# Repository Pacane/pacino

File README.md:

# Pacino

A hand-wired wireless split keyboard you print, screw together and solder — no main PCB.
Parametric OpenSCAD case + switch plate, with a build pipeline that produces **real STEP solids**
(via FreeCAD) so everything is editable in Fusion 360 as B-rep geometry, not as a mesh.
If you would rather not hand-wire it, the same design has a **slim build**: an 11.5 mm case around a
reversible PCB that is generated from this model and ready to order — [see below](#the-slim-build-a-real-pcb-115-mm).

Named after (and descended from) the [cheapino](https://github.com/tompi/cheapino), whose column
stagger and thumb-cluster geometry it borrows; hardware-wise it runs a nice!nano-compatible
nRF52840, Kailh hot-swap sockets on Amoeba-King single-key PCBs, and ZMK.

*20 keys per half (40 total): 5 columns + 2 extra keys, with the nice!view display. 145 × 120 mm.*

*23 keys per half (46 total): the optional 6th outer column, same display. 164 × 120 mm.*

*The minimal build — 18 keys per half (36 total), no extra keys, no display. 145 × 120 mm.*

All three are the same scale. The display costs no width: stacked over the nano, a build with it is
exactly as wide as one without. Renders of every other combination are
[at the bottom](#variant-gallery).

*The slim build: the same 40 keys over a reversible PCB, **11.5 mm** to the plate top instead of 17.5,
and flat — the cell lies in a well under the board. The controller sits flush in the plate window.*

**The default design:** a cheapino-style 3×5 (+2) + 3-thumb column-stagger layout on a clean
19.05 mm **MX** grid with **1.25u thumbs**, an **electronics bay** beside the inner column that
holds a **LiPo** (sunk into a well in the case floor — a 902030 by default), a **nice!nano**
(**flipped component-side down** in a cradle that is part of the plate, fully enclosed, USB out
through a notch in the wall) and a **reset button and power slide switch** in pockets in the
plate, laid out for **hand-wiring**. A **nice!view** mount (flush in the plate *directly over* the
nano, clamped by a screw-down bezel, so it costs no extra width) is in the model but off by default:
mounting bosses live in the walls, not in the matrix, and there is ~3 mm under the switch pins.
A PCB-sandwich build is a switch away.

```
keyboard.scad            the model — all parameters at the top, Customizer-friendly (parts: case, plate, section; bezel with nice_view)
layouts/cheapino.scad    generated from ../cheapino/pcb/cheapino.kicad_pcb  (exact positions, if you want them)
layouts/badtemper.scad   generated from ../badtemper2/BadTemper.kicad_pcb
tools/kicad_layout.py    KiCad .kicad_pcb -> layouts/*.scad  (switches, holes, MCU, Edge.Cuts polygon)
tools/pcb_gen.py         the slim build's PCBs: model -> pcb/*/ boards + footprint libs + gerbers
pcb/flat/  pcb/pod/     those two KiCad projects (generated, DRC-clean; each has its own README,
                         gerber zip and renders).  part = "pcb_test" prints a stand-in to fit first
tools/csg2step.py        OpenSCAD .csg -> STEP, runs inside FreeCAD
tools/svg_polygon.py     helper: bakes the cavity outline to a polygon for the FreeCAD pass
build.sh                 builds everything into out/
out/                     STEP / 3MF / STL / DXF / PNG — regenerate any time, never hand-edit
CHANGELOG.md             what changed since you printed — and whether you need to reprint, re-order or reflash
```

## Pick a ready-made variant

[`variants/`](variants/) holds every combination of the four options — 5 or 6 columns, with or
without the two extra keys, 902030 or 103450 battery, with or without nice!view — each as
`case_*` / `plate_*` STEP + 3MF for both halves (plus a bezel for display versions) and previews.
The index in [`variants/README.md`](variants/README.md) lists sizes; `./build_variants.sh`
regenerates them all.

## Quick start

```sh
./build.sh            # everything: step, mesh, dxf, png  (~40 s)
./build.sh step       # just the STEP files
SCAD_ARGS='-D battery=[34,50,10.5]' ./build.sh    # any parameter override, e.g. the 2000 mAh cell
```

Or open `keyboard.scad` in OpenSCAD and use the Customizer (`Window ▸ Customizer`).
`part` selects what is shown/exported (`assembly`, `section`, `case`, `plate`, the 2D profiles),
`side` picks `left` / `right` / `both`, `explode` lifts the plate.

Outputs per side: `case_*` and `plate_*` as `.step` (Fusion) and `.3mf` / `.stl` (slicer),
`*_2d_*.dxf` profiles for sketches, and `preview_*.png` (assembly, exploded, top, case, plate,
both halves, section through the bay). `WITH_DISPLAY=1 ./build.sh` additionally builds the
nice!view version (`case_display_*`, `plate_display_*`, `bezel_*`); in the Customizer that is the
`nice_view` switch.

## The layout

`grid_stagger = [0, 10, 16.4, 10, 7.5]` is the cheapino's column stagger (its PCB is already
19.0 mm MX pitch) snapped to 19.05. The thumb cluster starts where the cheapino's does
(`71.5, -15.5`) but uses **1.25u caps standing portrait** — long side pointing up at the columns —
fanned −10° / −22° / −34° around the thumb (key rotation = 90° + fan) at a 21.8 mm pitch along
the arc: `[[71.5,-15.5,80,1.25], [92.5,-21.5,68,1.25], [111.7,-31.7,56,1.25]]`. That gives
~1.5 mm between caps at their lower ends (they diverge towards the top, as a radial fan does) and
1.7 mm to the bottom row. Edit `grid_thumbs` to shift or re-fan the cluster; keep the rotation
as 90 + fan so the caps stay portrait.

**Extra keys.** `grid_extra_keys = [[1, -1], [2, -1]]` adds a short fourth row under the ring and
middle columns (under X/C on the left half, ,/. on the right) — 38 keys per pair. `[]` removes them;
any `[column, row]` pair on the grid works.

**Sixth column.** `grid_outer_col = true` adds a column outside the pinky (Corne-style 3×6), with
its own `grid_outer_stagger` (0 = same as the pinky). The left-edge bosses and bumpons follow it; the
half grows to 164 mm wide. Build it alongside the default with
`SUFFIX=_6col SCAD_ARGS='-D grid_outer_col=true' ./build.sh`.

**Hand-wiring.** Eight 6 mm bosses sit 0.5 mm inside the inner wall line so they merge into the
wall and the whole matrix area is free for diodes and wires (each boss was checked for ≥ 2 mm to
every switch body, ≥ 1 mm to the battery, and clear of the MCU cradle and the keycap footprints
so the screw heads are reachable). Under the plate there are 10 mm: MX body + pins take 8.3 from
the plate top, leaving ~3 mm under the pins. The bay has ~8 mm of floor to the right of the battery and 4 mm below it for routing,
and its open fence end faces the nice!nano.

Set `layout = "cheapino"` or `"badtemper"` to use the exact positions extracted from those
boards instead (`cavity_from = "pcb"` then follows that board's Edge.Cuts).

## The electronics bay

```
bay_left / bay_top_y = 86.5 / 61   the bay hangs from its top edge (USB at the top); size is automatic
battery_type = "902030"            the cell (902030 / 103450 / 604060 / custom), bottom-left of the bay, in a 3 mm fence
mcu_size   = [18, 33]              nice!nano at the top of the bay over the battery (measured on a SuperMini clone)
nv_pcb     = [14, 36, 1.6]         nice!view, right of the nano, header end down
ctrl_bay_h = 13                    reset + power strip hung below the bay, switches at its right end
```

Stack at the bay with the 902030 (z from the case underside): floor 0–2.5, with the battery well
sunk to 1.2 · battery 1.2–10.7 · 2.8 clearance for the nano's components, which now face down ·
nice!nano PCB 13.5–15.05 · 0.95 air · plate 16–17.5. The 1.3 mm the well recovers pays for the
component clearance the flip costs, so overall height is unchanged. The model warns if the board's
components would hit the battery or the board would hit the plate. `part = "section"` renders the stack as a 2D cut.

`battery_type` picks the cell and sizes the bay and the cavity depth (`cavity_depth = 0` = automatic,
battery thickness + 4): `902030` (20 × 30 × 9, 500 mAh — weeks per charge; 13.5 mm cavity),
`103450` (34 × 50 × 10, 2000 mAh; 45 × 60 bay, 14.5 mm cavity, +1 mm case height and +3 mm width — the bay reaches past the thumb cluster), `604060` (40 × 60 × 6; 10.5 mm cavity),
or `custom` with `battery_custom`. Build the 2000 mAh version alongside the default with
`SUFFIX=_2000mah SCAD_ARGS='-D battery_type="103450"' ./build.sh` → `case_2000mah_*`, `plate_2000mah_*`.
The controller charges at 100 mA by default, which is ~20 h for the 2000 mAh cell: before you fit it, bridge the
**boost** solder jumper on the back of the board (two pads by the battery pads; 500 mA on a nice!nano v2, 300 mA
on the SuperMini clones — only with a cell over 500 mAh, so not for the 902030 or 303040).

### How the nano and the battery are held

**Battery:** it drops into a **well sunk 1.3 mm into the case floor** (`battery_well_floor`), whose
walls locate it on all four sides; with the plate on, the nano 2.8 mm above it keeps it in the well. Set `battery_well_floor = 0`
instead and it sits on the floor inside a 3 mm printed fence (`battery_fence`, open at the lead end),
which costs 1.3 mm of case height — the well is the default because the flipped nano needs the room.

**nice!nano / nRF52840 clone:** it goes in **upside down** (`mcu_flipped`, the default) — components
and USB connector facing *into* the case, bare PCB back facing the plate. That protects everything on
the board, and because the wires now poke straight down through the pads into the bay, the cradle no
longer needs wire channels along the sides: the plate above it is **solid**, with no opening over the
MCU at all.

It sits in a cradle that is part of the plate: rails on both long sides, open at the USB end,
holding the board four ways —

- **sideways:** five half-round **crush ribs** per rail (`crush_rib`, 0.6 mm proud, centred on the
  pocket wall so nothing bulges outward), narrowing the 18.6 mm slot to **17.4 mm** at the ribs. An
  18.0 mm board goes in with real resistance and shaves them to a custom fit; boards up to ~18.6 mm
  crush them further. Turn `crush_rib` down for a lighter fit, up for a tighter one.
- **from below, far end:** two corner tabs under the outer 0.5 mm of the far edge, with a 10 mm gap
  between them so a SuperMini-style clone's centred reset button stays clear.
- **from below, USB end:** two posts rising from the **case floor** (`mcu_end_post`), which engage
  once the plate is screwed down.
- **from above:** a 6 mm-wide roof pad on the plate over the bare back of the board, leaving it
  0.2 mm of lift.

**To fit it: with the plate off the case, slide the board into the cradle from the open USB end
until it meets the far rail.** To remove it, push it back out through the **4 mm eject hole** in the
far rail. **Set `mcu_size` to your board's real width × length.** Before printing, check your board's
component side is clear where the cradle touches it: the far corners (outer 0.5 mm, either side of
the reset button) and the two USB-end corners.

**Wiring the nano:** solder the wires on what is now the underside — they drop straight into the bay,
no channels or routing needed. The battery leads come up out of the well right below the board.

Setting `mcu_flipped = false` restores the old component-side-up cradle: an opening through the
plate, wire channels along both long edges, and a USB slot that crosses the plate line.

### Reset button and power switch

Plain through-hole parts, both dropped into the plate from above: a **12 × 12 mm tactile switch**
with a tall plunger (reset → nano `RST` + `GND`) and an **SS12D00 slide switch** (power, in series
with the battery `+` to the nano's `B+`). Each pocket is a hole through the plate the size of the
body (+0.2 mm) with a 1.2 mm floor hanging below, with a 3.5 mm square opening around each leg
(`ctrl_leg_hole`) so the legs hang in free air below the floor and a wire can be wrapped and
soldered to them from underneath. The
tactile's body sits 2.3 mm below the plate top so ~1 mm of its 3.3 mm plunger is proud — enough to
press, hard to hit by accident; the slide's 3 mm actuator stands up for your thumbnail. Solder
wires to the legs from below. Nothing can push the parts in (they sit on the floor) and the legs
plus wires keep them from lifting; if you want belt-and-braces, a dab of glue or a 0.1 mm tighter
`ctrl_clearance` does it. `reset_body` / `power_body` / `*_legs` take the dimensions of whatever
switches you actually buy.

They sit in a **control bay** strip hung below the electronics bay (`ctrl_bay_h = 0` sizes it for
the larger switch), placed as high as the battery allows — the pockets reach up into the bay's
battery-free margin — so they stay clear of the thumb keys in both battery layouts, off the battery
(legs and wires hang free below), and add nothing to the bay's width. (The strip spans the full bay width on purpose: a narrower one leaves a pocket
between bay, column 4 and thumb key 2 that the outline smoothing turns into a hole.)

### nice!view

The nice!view has no mounting holes — on a PCB it hangs off its 5-pin header — so here it is
**clamped**. It sits vertically (header end down, the way a Corne shows it) in a pocket through the
plate, resting on two 1 mm ledges under its long edges that hang from a ring below the plate. The PCB
top ends up `nv_preload` (0.15 mm) above the plate top; the printed **bezel** (`part = "bezel"`,
2.5 mm, window sized to the glass) is screwed down onto two 5 mm bosses hanging under the plate with
M2 screws — `nv_boss_hole_d = 1.7` for self-tapping into PETG (works well; 3 mm of engagement), or
3.2 for heat-set inserts — so it clamps the PCB, not the plate. The 12.6 mm opening under the
display leaves the solder pads free. Nothing can come loose without removing two screws, and
nothing relies on a friction or snap fit.

**It sits directly on top of the nano** (`nv_stacked`, the default). That only works because the
board is flipped: the plate above it is solid, so the display can take that surface. The bay then
stays as narrow as the no-display version — the display costs **0 mm of width** instead of 11.6.

Three things follow from stacking, and the model enforces all of them:

- The bezel's screw bosses move from the display's **ends to its sides** — an end boss hangs 3 mm
  below the plate and would pass straight through the board. On the sides they clear the board by
  0.8 mm and the cradle pocket by 0.5 mm, landing in free bay space 2.3 mm above the battery.
- The support ledges are thinned (`nv_ledge_te`, 1.2 → 0.6 mm) so they clear the board's back by
  0.4 mm — and they then double as the board's hold-down, replacing the cradle roof pad that the
  display's opening cuts through.
- The display's wiring end overhangs past the board, so its five wires drop straight into the bay
  and run to the nano's pads, which now face into the bay.

The cost is servicing: getting the nano out means removing the bezel and lifting the display first.
Set `nv_stacked = false` for the old side-by-side bay (11.6 mm wider); it is also the automatic
behaviour if `mcu_flipped` is off, since an unflipped nano needs that plate area for its own opening.

### Bumpons

Eight 10.6 mm × 1 mm recesses in the underside for 10 mm self-adhesive rubber feet (`bumpon_d`,
`bumpon_clearance`, `bumpon_depth`; `bumpon_positions` for the four under the key block and thumb
cluster, two on the left edge follow the outer column, and two are placed on the bay: 8 mm in from
its top-right corner, and 12 mm up from the bottom of the control strip on the right). The floor is
2.5 mm so 1.5 mm remains under each recess.

The two bay feet and the **battery well** compete for the same floor: the well is already 1.3 mm
into it, so a recess over the well would leave 0.2 mm. With a well the cell therefore sits against
the bay's *left* wall (which doubles as the well's side) instead of 5 mm from it, keeping the bay's
right-hand corners clear, and the bay is sized so the top-right foot always fits beside the cell with
a millimetre of wall outside its recess. Each bay foot then moves outward only by what its well
forces — a couple of millimetres — and the model warns if one has nowhere to go. The wider cells pay
for it in width: the 103450's bay is 45 mm instead of 44, and its case 148 mm. A 56 mm MagSafe magnet ring (the
self-adhesive kind) goes under the index column (`magsafe_d`, `magsafe_pos`; 0 = none). It is **printed in**
(`magsafe_style = "embedded"`, the default): an annular pocket exactly as tall as the ring (`magsafe_ring_id`,
`magsafe_ring_t`; measure your ring — a 56 mm sticker ring is about 45 mm inside and 0.5–0.7 mm thick), open to the
underside through a window one layer up, so the first layer is a ledge overlapping the ring's edges by 0.8 mm
(`magsafe_lip_w`) and the steel shows through between them, 0.2 mm below the surface. Add a pause in the slicer
**before layer 5** (the model prints the height: after the layer ending at z = 0.8 mm), drop the ring in with its
exposed face **down** and the adhesive up, press it flat, and resume. Layer 5 is then laid straight onto the ring,
like a first layer on a sticky bed, with the nozzle a full layer above the steel. If supports are on, put a
support blocker over the ring: the pocket reaches the plate through the window and would otherwise be filled.
It uses 0.8 mm of the 2.5 mm floor, so it works in the slim build too, and the ring cannot come off. Being
steel, the ring has no polarity to get wrong.

Why the window: the hold improves with every tenth of a millimetre less between the ring and the mount. A
0.4 mm skin over the ring (`magsafe_skin = 0.4`) is the clean look and holds decently; a one-layer skin held
better but tears along its lines with the ring's edge behind it; the ledge is backed by the pocket wall and holds.
Don't leave air over the ring either (`magsafe_pocket_air` only pads a ring thinner than a layer multiple; keep
ledge or skin + ring + air on a layer boundary, the model notes if it isn't): the ceiling would have to bridge it,
and since a layer's lines all run one way, the ones running along the ring span 30 mm chords and sag. The bigger
lever is the ring itself: the usual sticker ring is 0.65 mm of steel, and a *magnet* ring (1.2–2 mm, 16 segments)
holds a mount in a different league — the pocket takes it the same way, but it has a right way up: hold it
against the mount first and put the face it pulls in with down.

The two stick-on alternatives: `"groove"` leaves the underside flat with a one-layer locating groove 0.3 mm
outside the ring's edge, and the ring's adhesive sticks straight to the bed-side first layer (it holds there, as on
any PETG print). `"recess"` sinks the ring 1 mm into the floor (`magsafe_depth`), but that pocket prints on
support and the adhesive does *not* hold on a support-interface surface — sand the pocket and glue the ring in.
The recess has to stay clear of the battery well, since the two cut the floor from opposite sides and would leave
0.2 mm where they overlap (the model warns). `out/preview_bottom.png` shows them all.

### How the plate attaches

The plate is the lid. The case walls end flush with the plate's underside, so the plate rests on
them all round; a 1 mm lip under the plate drops inside the walls (0.2 mm clearance) and locates it.
Eight 6 mm bosses rise from the floor to the plate underside (six around the key block, two on
the bay's right-hand corners, all half-buried in the wall so they don't intrude on the wiring), each with a
3.3 mm × 5 mm hole, with a 4.2 mm × 0.6 mm counterbore at its mouth (`boss_relief_d` / `boss_relief_h`), for an **M2 × 4 × 3.5 brass heat-set insert** — press it down until it bottoms in the counterbore, so it and the plastic it displaces sit below the boss face and the plate seats without trimming (`boss_hole_d = 1.7` if you'd
rather self-tap). **M2 × 6 screws** go down through the plate into them — the heads sit on top of
the plate, like a tray-mount case (ultra-thin hex-socket heads are ideal).

Hardware per half: 8 × M2×4×3.5 inserts, 8 × M2×6 screws, 8 × 10 mm bumpons
(+ 2 × M2×4 self-tapping screws for the bezel if you build the display version).
`variants/insert_test.3mf` (`part = "insert_test"`) is a two-minute test print — one boss as on the
case and a scrap of plate with its screw hole — to try the insert and screw before printing a case.

**M3 instead:** `screw_size = "M3"` resizes everything at once — 4.0 mm insert holes for the common
4.2 mm OD M3 inserts with a 5 mm counterbore, 3.4 mm clearance holes in the plate, and in the slim build a
6 mm spacer boss, a 4.6 mm wall channel, a 3.6 mm wall and 3.4 mm board holes. Hardware is then
8 × M3 inserts (4 mm long here, 3 mm in the slim build) and 8 × M3×6 (M3×10 slim) screws; an M3 socket
head is 5.5 mm across, so use low-profile ones. The 6 mm bosses keep 1 mm of wall around the insert —
fine for the five buried in the wall, set the three free-standing ones carefully. The bezel stays M2.

### Hot-swap with single-key PCBs

Per-key hot-swap PCBs (amoeba style) work as-is: the Kailh socket and the diode go on the underside
of each little board, the bare top face sits against the switch body, and the board hangs on the
switch — the socket grips the pins (as in any hot-swap board) and 5-pin switches' pegs locate it.
Row/column wires join the boards' `ROW`/`COL` pads underneath, below the ribs.

The classic failure with hanging boards — a switch being inserted pushes the board down instead of
into the socket — is handled by **pillars rising from the case floor** under each board's four
corners (`key_pcb_post = [2.5, 3.2]`, `key_pcb_post_gap = 0.2`). They sit inside the corner notches,
on the bare 1.3 × 2 mm patches the amoeba-king keeps clear of pads and components (its side pad rows
end 5.6 mm off-centre; the pillars start at 6.3), and stop 0.2 mm below the boards, so with the case
closed a board cannot move and a new switch's pins are forced into the socket. To swap a switch,
just pull and push with the case closed; the board stays put.

**Wiring around the pillars.** The pillars hug the *top and bottom* edges of each board (the row
boundaries), 3.5 mm long at ±7 mm from centre, so the column boundaries are completely free and the
centre 10 mm of every row boundary is free too. The amoeba-king's ROW pads are on its left/right
edges and its COL pads at the centre of its top/bottom edges: row wires go straight across the
column boundary pad-to-pad, column wires run down the board centre line between the pillar pairs —
neither comes near a pillar. The only rule: never lay a wire along a board's top/bottom edge into a
corner, because a wire on a pillar patch gets clamped in the 0.2 mm gap when the case closes.
[`docs/wiring_guide.png`](docs/wiring_guide.png) shows the underside: the inner wall and its bosses,
the boards with their pads, the pillars, the matrix, and the nice!nano with every pin named. The
matrix pins are read straight from the shield (`row-gpios` in `pacino.dtsi`, `col-gpios` in
`pacino_left.overlay`), and each row and column chain gets its own thin wire to its pin, routed
clear of pillars, bosses and wall (`tools/wiring_guide.py` regenerates it and checks every wire;
each variant directory gets its own). Orient the boards with the ROW pads towards the neighbouring
columns (the pillars are sized around that). The row wires leave the inner column straight into the
bay; the column wires collect at the thumbs' COL pads (the bottom key's, for a column without a
thumb), enter the bay beside the inner column's bottom corner and climb the far side of the nano.

`key_pcbs = true` (default) also stops the ribs 0.3 mm above the boards' top face, since the boards
are wider than the rib cells; set it to false for plain hand-wiring (no boards, no pillars). All of
this is a hand-wired idea — `build = "pcb"` ignores it, and takes its rib depth from the main board.

### Plate stiffness

A flat 1.5 mm PETG plate flexes under typing, and infill/walls can't fix that (it is already
practically solid). The plate therefore carries an **egg-crate of ribs** on its underside:
a 1.5 mm wall around every switch, 3.2–3.5 mm tall (down to the switch-body bottom, or 0.3 mm above
per-key PCBs, or the main board on the slim build), 0.3 mm outside the switch's clip zone, merging
into a grid (`plate_ribs`, `rib_w`, `rib_h`). That is roughly 5× the bending stiffness of the flat plate
at no change in case height — the ribs sit beside the switch bodies, above the pins, so wiring and
diodes (which live below the pins) are unaffected. The ribs are kept clear of the bosses and the
lip. Print the plate in 100 % infill anyway; a PLA plate with a PETG case is also a fine
combination (PLA is ~70 % stiffer than PETG).

### Printing (PETG)

- **Case:** prints as-is, bosses up, with a **pause before layer 5** to drop the MagSafe ring into its pocket
  (see [Bumpons](#bumpons)). If you print with supports on (say, for the bumpon recesses), use `case_*.bambu.3mf`
  instead: the same case as a Bambu Studio / Orca project with a support blocker already over the ring pocket
  (`tools/bambu_3mf.py` makes it from the plain 3MF) — otherwise the slicer fills the pocket through its window.
  Nothing overhangs except the open-top USB slot (bridged by the
  plate, so it can stay open) and the 1 mm bumpon recesses on the first layer.
- **Plate:** print top-side down. The cradle, the switch pockets (and the display ring and bezel
  bosses, if enabled) then point up and need no support; the keycap side gets the smooth first
  layer. The cradle's crush ribs run the full rail height, so they print as part of the rail
  perimeter. The only overhangs are the cradle's far corner tabs, the roof pad over the board and
  the pocket floors (tiny, fine in PETG).
- **Bezel** (if used): window side down.
- PETG tolerances: pockets have 0.2–0.3 mm clearance, the plate lip 0.2 mm; if your printer runs
  tight, bump `mcu_clearance` / `ctrl_clearance` to 0.4 and `lip_clearance` to 0.3. The MCU cradle
  is deliberately an interference fit — tune `crush_rib` (0.6) rather than the clearances. Self-tapping M2
  into 1.7 mm holes is a good fit for PETG; heat-set inserts also work in the 5 mm bosses.

### What sets the size

Per half (case outline), against the Bad Temper:

| | width × height |
|---|---|
| Bad Temper (choc, printed case) | 122 × 94 |
| badtemper2 MX PCB + 2 mm case | 131 × 107 |
| this (default, no display) | **145.0 × 120.2** (17.5 mm to the plate top) |
| this, with nice!view | 145.0 × 120.2 (the display stacks over the nano) |
| this, slim PCB build | 145.0 × 120.2 (**11.5 mm** to the plate top, flat; or the same with a pod for a 902030) |

Without the display the bay (nano + 902030) is narrower than the thumb cluster, so the **thumb
cluster** sets the right edge (130.5) and the bottom (−51): the cheapino position plus the portrait
1.25u fan is +12 mm lower and ~+12 mm further out than the Bad Temper's 1u thumbs. The display no
longer changes that: stacked over the nano it needs no extra bay width, so both versions are the
same size. (Side by side — `nv_stacked = false` — the nano + nice!view row is 41.2 mm and pushes
the right edge to 142.1: **+11.6 mm**.) Margins (`key_margin` 3,
`wall` 2.4) account for ~2.5 mm per side. A Bad Temper-sized half therefore needs a tighter thumb
cluster, not a different battery.

## Getting it into Fusion 360

1. **STEP (recommended).** `File ▸ Open` / `Insert ▸ Insert Derive` on `out/case_left.step`.
   One solid, true planar faces, real cylindrical holes. Edit with `Press Pull`, fillets,
   `Move Face`, or sketch on a face and cut/extrude; everything after import is in the timeline.
   Volumes are cross-checked against OpenSCAD's mesh on every build (printed by `build.sh`;
   they agree to <0.01 %).
   Note the case outline is a polygon (8 segments per 90° of rounding) because OCC's 2D
   offsetting cannot reproduce OpenSCAD's outline smoothing — see `build.sh`. Holes and bosses
   are exact cylinders.
2. **DXF profiles → fully parametric rebuild.** `Insert ▸ Insert DXF` on the XY plane:
   `cavity_2d`, `case_outline_2d`, `plate_2d`. Extrude the outline to the wall height, cut the
   cavity from `floor_t` up, add bosses at the hole centres. Slower, but you own every dimension.
3. **Mesh fallback.** `Insert ▸ Insert Mesh` with the `.3mf`, then `Mesh ▸ Convert Mesh`
   (Prismatic).

## Build modes and hardware

- `build = "plate"` (default, hand-wired): switches clip into the 1.5 mm plate, 6 mm bosses run
  from the floor to the plate underside with 3.3 mm holes for M2×4×3.5 heat-set inserts
  (`boss_hole_d = 1.7` for self-tappers); M2×6 screws through the plate (`screw_size = "M3"` for
  M3 inserts and screws throughout). `cavity_depth = 10`
  leaves room for MX bodies + pins + wiring and the battery/cradle stack.
- `build = "pcb"`: PCB sandwich, and the slimmest build at **11.5 mm**. Bosses stop at the PCB
  underside, the plate gets spacer bosses down to the PCB, MX plate-to-PCB spacing is automatic
  (5.0 mm MX / 2.2 mm Choc), the MCU sits on sockets on the PCB, the plate gets a window instead of
  the cradle, and the cell either lies flat under the board or rides in a pod on the plate over the
  controller. The boards are in [`pcb/`](pcb/) — see
  [The slim build](#the-slim-build-a-real-pcb-115-mm).
- `switch_type = "choc"` swaps pitch (18 × 17), cutout (13.8), plate thickness (1.3) and heights.
- Wall cutouts: `usb_cutout = [w, h, z-offset-from-board-top]`; `extra_cutouts` for a power
  switch etc. `[x, y, outward_angle, w, h, z]`.

## Using a different PCB or layout

```sh
python3 tools/kicad_layout.py path/to/board.kicad_pcb --prefix mykbd > layouts/mykbd.scad
```

It picks up `SW*`/`K*`/`MX*` switch footprints (position, rotation), mounting holes with
1.9–3.6 mm drills, `U1` as the MCU, and chains `Edge.Cuts` into one polygon. Add an `include`
and a `layout` option in `keyboard.scad` the way `cheapino`/`badtemper` are wired in.

## The slim build: a real PCB, 11.5 mm

`build = "pcb"` turns the same design into a **PCB sandwich**, and the boards exist: [`pcb/`](pcb/)
holds two complete, DRC-clean KiCad 9 projects with gerbers, generated from this model by
[`tools/pcb_gen.py`](tools/pcb_gen.py).

*The same board from both sides. Flip it over and the bay swaps sides — that is the right half. Each
face's silkscreen names the half you build on it, and outlines its hot-swap sockets the way round
they go in on that half. These renders come out of `tools/pcb_gen.py` with the board, so they are
always the board in the repo rather than a picture of an older one.*

**11.5 mm to the plate top** — the floor for any MX build, and 6 mm thinner than hand-wired. The
stack is 2.5 floor + 2.4 (hot-swap sockets) + 1.6 board + 5.0 (MX plate-to-PCB, fixed by the
switch), and there is nothing left to remove.

Hardware for the slim build: the bosses stop at the board, so they are only 4.9 mm tall and their insert
holes 4 mm deep with 0.9 mm of floor under them, the same 0.6 mm counterbore at the mouth — use **M2 × 3 × 3.5 heat-set inserts** (the hand-wired case
takes 4 mm ones) and **M2 × 10 screws** (1.5 plate + 3.5 spacer + 1.6 board + 3 mm of thread). Five of the
eight bosses sit on the wall line like the hand-wired ones, and since the wall keeps rising 5 mm past their
tops, their insert holes would be tucked 1.2 mm under it — so a 4 mm channel (`pcb_screw_channel`) runs up
the inside of the wall over each hole, the insert and screw drop straight in, and the slim case's wall is
3 mm (`pcb_wall`) to keep 1.5 mm behind the channel (`screw_size = "M3"`: 4.6 mm channel, 3.6 mm wall, 3.4 mm
board holes, 6 mm spacer bosses — see [How the plate attaches](#how-the-plate-attaches)). The other three (thumb end, the bay's bottom corner, and
the one by the thumb keys) stand 2.5–3 mm clear of the wall as full round bosses; the board gets three real
mounting holes there and five edge notches at the wall-line ones. Two 3 mm floor pillars (`pcb_posts`)
stand under the board between the bosses, in the column gaps clear of the sockets, switch pins and diodes,
so a 55 mm span of board is not hanging on its corners; the model warns if one is moved onto a socket, and
the board generator keeps diodes off them.

Going to M3 with a board that was made for M2 (2.2 mm holes): the screws only have to pass *through* the board,
so drill its three real holes and file its five edge notches out to 3.4 mm rather than ordering a new one. Seven
of the eight have no copper within 3.15 mm of the hole centre (only the ground pour, which any drill over 2.7 mm
exposes on the hole wall — harmless, the screw lands in a brass insert in plastic). The top-edge hole between the
middle and ring columns, at (76.2, 57.1), is the exception: the column-0 bus runs 1.45 mm from its centre on the
back, so a 3.2 mm drill would cut it. Leave that one M2 with `m2_holes = [[76.2, 57.1]]` (its insert hole,
counterbore, plate hole and board notch stay M2-sized) or leave it unscrewed — the plate rests on the wall all
round. A board generated with `screw_size = "M3"` (`tools/pcb_gen.py -D 'screw_size="M3"'`) has 3.4 mm holes
from the start.

What sets it is where the cell goes, because **below the board every millimetre of battery is a
millimetre of case**. Above it, the 3.5 mm the MX geometry hands you is free — the socketed
controller already lives there, finishing flush with the plate top, and costs no height at all.
There are two ways to spend that, and both are built:

### Flat — a 303040 under the board (the default)

There is 3.4 mm of unused space under the board in the bay: 1.3 mm of floor well plus the 2.4 mm the
hot-swap sockets need — and the bay has no switches, so nothing is using it. A cell that fits inside
it needs no pod and no cutout in the board. A **303040** (3 × 30 × 40, ~320 mAh) lies in a well in the
floor, the plate stays flat, and the controller sits flush in its window.
Parts: [`variants/5col_extra2_bat303040_pcb_flat/`](variants/5col_extra2_bat303040_pcb_flat/),
board: [`pcb/flat/`](pcb/flat/).

3.4 mm is a cliff, not a slope. A thicker cell has to poke up through the board, and in the bay that
cutout runs straight under the controller and leaves its pin rows with no board to solder to — the
model warns if you ask for it.

### Pod — the 902030 over the controller

If you want the full 500 mAh, the 902030 rides in a **pod moulded into the plate, directly over the
controller** (`battery_pod = true`): in through the MCU window from below, resting on the controller,
leads down into the bay. Same 11.5 mm case, same outline — the pod stands 11.1 mm proud of the plate,
under the keycaps, which reach 14.5.
Parts: [`variants/5col_extra2_bat902030_pcb_pod/`](variants/5col_extra2_bat902030_pcb_pod/),
board: [`pcb/pod/`](pcb/pod/).

*Every part and where it sits, in the order you assemble it. `part = "section"` cuts the stack at
`section_x` (here 111, through a thumb key and the bay at once); `explode` separates the layers —
case, cell, board, controller, plate, switches, keycaps — each by its own step, so `explode = 0` is
exactly the assembled model.*

### Test-fitting it before you order a board

`part = "pcb_test"` prints a stand-in for the PCB: the real outline and mounting notches at 1.6 mm
thick, every hole a switch's pins, pegs and centre post pass through, the controller's two socket
rows, and the reset and slide switch legs — plus bumps on the underside at the hot-swap socket's real
1.85 mm, so the 2.4 mm under the board is a real test and not an assumption. Both slim variants ship
one as `pcb_test.3mf`; it is reversible the same way the board is, so flip it over for the other half.

```sh
SCAD_ARGS='-D build="pcb"' ./build.sh          # the case and plate
openscad -D 'part="pcb_test"' -D 'build="pcb"' -o pcb_test.3mf keyboard.scad
```

Print it flat, bumps up, then turn it over into the case. It checks the outline against the walls
and bosses, that every switch's pins land in a hole, the plate-to-board spacing, where the controller
and the two switches sit, the cell's room, and the 11.5 mm — everything except the copper. What it
cannot tell you: a printed 1.6 mm sheet is floppier than FR-4, so don't judge flex by it.

### The board

20 keys, 39 nets, ~515 tracks, ~16 vias, two layers, 0.3 mm tracks / 0.2 mm clearance / 0.3 mm
smallest drill — the cheapest process any fab offers. Hot-swap sockets, SOD-123 diodes (a
through-hole 1N4148 fits the same land), the controller on 3.5 mm machined low-profile sockets under the
plate window, reset and slide switch poking up through theirs. The controller gets **bare machined pins**
(Mill-Max 3320 or diode legs) — not a pin header with a plastic body: the board has to sit directly on the
sockets, 3.5 mm + its own thickness putting its back flush with the plate top and its USB receptacle inside
the socket gap. A 2.5–3 mm header body between board and sockets lifts the whole controller by that much and
pushes the USB receptacle up into the plate at the wall. The window around the controller runs right up to the
wall line at the USB end (the receptacle overhangs the board there) and the plate's rim is cut away across the
whole window at that end (the wall's notch below stays 12 mm), so the port is open from above rather than hidden
under a bridge and no stub of rim sits over the board's corners (`usb_plate_slot`); the window has 2 mm of clearance on the other sides;
`part = "clash"` renders whatever the plate hits — it should be empty. The silkscreen outlines every
hot-swap socket on both faces, so each one goes where its outline is — and because the outlines on
the two faces are the 180° rotation of each other, the way the right half differs is visible on the
board rather than only in the instructions.

The two builds are **two boards**, not one board with an option: moving the cell moves the bay, two
of the mounting holes and the reset/power positions. They are otherwise identical — same matrix,
same footprints, same firmware; only the bay end of the outline and the parts in it differ.

Both are **reversible**: one design, flipped over for the right half. Three things pay for that, and
each board's `README.md` has the detail —

- **Switches** carry *both* MX pin diagonals and a socket land on each face; on the right half they
  go in rotated 180°, which an MX switch does not care about. (Mirroring the pin pair instead — the
  obvious way — puts two 3 mm holes 2.84 mm apart and they merge into a slot.)
- **The matrix** lands on different GPIOs per half, because flipping swaps the controller's two pin
  rows. The ten holes were chosen so both of each hole's pins are usable GPIOs, keeping
  `pro_micro 1/14/15/16` free on both halves. Hence a separate `pacino_pcb` ZMK shield. (ZMK's
  stock nice!view adapter wants pins 1/2/3 — D1 plus the OLED header's SDA/SCL — and the PCB uses
  2 and 3 for the matrix, so a display on the PCB needs its own `nice_view_spi` on the free
  14/15/16.)
- **The controller** sits on top of the board — the face opposite the sockets — component side
  down, flush in the plate window; the pin lists and the **L**/**R** marks are worked out for that.
- **Power** gets two three-pad solder jumpers (bridge to **L** or **R**). Reset needs none: it sits
  across a pin pair that is GND/RST one way up and RST/GND the other.

```sh
tools/pcb_gen.py                 # both boards, footprint libraries and gerbers
tools/pcb_gen.py --variant=flat  # just one
```

Everything on them comes from `keyboard.scad` — outline, switch positions, mounting holes, controller
and switch placement — so changing the model and re-running moves the boards with it. There is no
schematic file: the generator declares every net and every connection, and names them the way the ZMK
shield does. Each project ships a `*_gerbers.zip` ready to upload; order ten and you have five
keyboards' worth of both halves.

If you would rather draw your own board, the bootstrap files are still there:
[`docs/pcb/pacino_edge_cuts.dxf`](docs/pcb/pacino_edge_cuts.dxf) (the outline for `Edge.Cuts`) and
[`docs/pcb/pacino_placement.csv`](docs/pcb/pacino_placement.csv) (every position in KiCad
coordinates), both from `tools/kicad_placement.py`. `tools/kicad_layout.py` reads a finished
`.kicad_pcb` back so the case can follow the real board.

## Variant gallery

Every option combination, with previews, sizes and download links:
**[variants/README.md](variants/README.md)** — each directory also carries an exploded-style
`preview_assembly.png`, a `preview_top.png` and its own `wiring_guide.png`.

## Firmware (ZMK)

This repo doubles as the ZMK config — no separate zmk-config repo needed. `config/` holds the
`pacino` shield (matrix, transform, default keymap) and `build.yaml` the build matrix; pushing a
change to either makes **GitHub Actions build the firmware** (Actions tab → latest run →
artifacts → `.uf2` files for left, right and `settings_reset`). SuperMini nRF52840 clones flash
as `nice_nano_v2`: double-tap reset, drag the `.uf2` on.

The slim PCB build has its own shield, **`pacino_pcb`** (same layout, same matrix, same keymap):
the reversible board puts the matrix on a different set of GPIOs on each half, so it cannot share
`pacino_left` / `pacino_right`. Both shields are in the build matrix; take the `pacino_pcb_*`
artifacts if you built the board. The pin lists are in
[`pcb/README.md`](pcb/README.md) and `tools/pcb_gen.py` prints them.

Electrical matrix ([`docs/wiring_guide.png`](docs/wiring_guide.png) draws it pin by pin) — 5 columns × 5 rows
per half, diodes `col2row` (Amoeba-King: switch → diode → ROW pad):

| matrix | wires to | nice!nano pin |
|---|---|---|
| row 0 / 1 / 2 | top / home / bottom key row | `pro_micro` 20 / 19 / 18 |
| row 3 | the two extra keys | `pro_micro` 16 |
| row 4 | the three thumbs | `pro_micro` 10 |
| col 0…4 | pinky → inner column (each column chain includes its extra key and thumb) | `pro_micro` 9 / 8 / 7 / 6 / 5 |

Pins 1, 2 and 3 are left free: that is where ZMK's stock `nice_view_adapter` puts the nice!view
(CS on D1, MOSI and SCK on the OLED header's SDA/SCL, plus VCC and GND), so the display variant is
this same wiring plus `nice_view_adapter nice_view` after the shield in `build.yaml` — no rewiring,
and nothing to add to `config/pacino.conf` (the nice_view shield enables the display itself). Pins
14/15/16 are the AVR pro micro's SPI pins; the nRF52840 puts SPI anywhere. Edit your keymap in
`config/pacino.keymap`. The left half is the central
side. The shield covers the default 5-column + 2-extra layout; the 6-column or no-extra variants
need a matching edit to the transform and one more column pin.

## Requirements

- OpenSCAD 2025.03+ (Manifold backend) — `/Applications/OpenSCAD.app`
- FreeCAD 1.0+ for STEP — `/Applications/FreeCAD.app` (only for `build.sh step`)
- Python 3 for the tools
- KiCad 9 for the PCB — `tools/pcb_gen.py` runs itself under KiCad's bundled Python (`pcbnew`)
  and uses `kicad-cli` for the gerbers

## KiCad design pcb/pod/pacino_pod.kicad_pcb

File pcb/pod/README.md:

# pacino_pod

The board for the slim build whose cell sits **in a pod moulded into the plate, directly over the controller**.
Cell: **902030 (9.5 x 20 x 30, 500 mAh)**.  Case half: [`variants/5col_extra2_bat902030_pcb_pod`](../../variants/5col_extra2_bat902030_pcb_pod/).

The two slim builds are two boards, not one board with an option: moving the cell moves the bay, two
of the mounting holes and the reset/power positions. The matrix, the footprints and the firmware are
identical between them.

Generated by [`tools/pcb_gen.py`](../../tools/pcb_gen.py) -- **do not hand-edit
`pacino_pod.kicad_pcb`**; change the generator (or `keyboard.scad`, which the outline and every
position come from) and re-run it. There is no schematic file: the generator declares every net and
every connection, and names the nets the way the ZMK shield names them.

    tools/pcb_gen.py                 # both boards, with gerbers and renders
    tools/pcb_gen.py --variant=pod  # just this one
    tools/pcb_gen.py --no-render     # skip the raytracing while iterating

20 keys, 39 nets, 580 tracks, 21 vias. Two layers, 1.6 mm, 0.3 mm tracks,
0.2 mm clearance, 0.3 mm smallest drill -- inside every fab's cheapest process.

## One board, both halves

The board is **reversible**: build the left half with the parts on the back, flip the board over and
build the right half with the parts on the front. The silkscreen on each face says which half it is.
Three things make that work.

**Switches.** Every switch footprint carries *both* MX pin diagonals -- the normal pair and its 180
degree rotation -- and a hot-swap socket land on each face. On the right half the switches and the
sockets go in **rotated 180 degrees**; MX switches are square and their stems are symmetric, so
nothing about the feel, the keycaps or the plate changes. (Mirroring the pin pair instead, which is
the obvious way to do it, puts two 3 mm holes 2.84 mm apart -- they would merge into a slot.)

**Matrix.** The controller sits on the face *opposite* the sockets and diodes -- on top of the board,
component side towards it, flush in the plate's window -- and flipping the board swaps its two pin
rows but not the position along a row, so each hole is one pin on the left half and a different one
on the right. The ten matrix holes were
chosen so that *both* of their pins are usable GPIOs and neither is one of `pro_micro 1/14/15/16` --
the nice!view's CS/MISO/SCK/MOSI stay free on both halves. The two halves therefore need different
pin lists in ZMK -- which is why the slim build has its own shield, `pacino_pcb`, whose two overlays
differ from each other (the hand-wired `pacino` shield is unchanged and unrelated):

| net | hole | left half | right half |
|---|---|---|---|
| `ROW0` | U1 pad 20 | `pro_micro 2` | `pro_micro 21` |
| `ROW1` | U1 pad 19 | `pro_micro 3` | `pro_micro 20` |
| `ROW2` | U1 pad 18 | `pro_micro 4` | `pro_micro 19` |
| `ROW3` | U1 pad 17 | `pro_micro 5` | `pro_micro 18` |
| `ROW4` | U1 pad 13 | `pro_micro 9` | `pro_micro 10` |
| `COL0` | U1 pad 5 | `pro_micro 21` | `pro_micro 2` |
| `COL1` | U1 pad 6 | `pro_micro 20` | `pro_micro 3` |
| `COL2` | U1 pad 7 | `pro_micro 19` | `pro_micro 4` |
| `COL3` | U1 pad 8 | `pro_micro 18` | `pro_micro 5` |
| `COL4` | U1 pad 12 | `pro_micro 10` | `pro_micro 9` |

**Power.** RAW and GND have no symmetric partner, so each gets a three-pad solder jumper: bridge the
centre pad to the pad marked **L** or **R** for the half you are building. The mark is printed on
the face the controller sits on (the face opposite the sockets), and that is the pad to bridge.
Boards generated before September 2026 have the letters the other way round: on those, still bridge
the marked pad on the controller's face, whatever letter it shows. Reset needs no jumper -- the
switch sits across the `(rowA,3)`/`(rowB,3)` pair, which is GND/RST one way up and RST/GND the
other; a 12 mm tactile links its two legs 12.5 mm apart internally, and the footprint puts those on
one net (boards from before the same date have it the other way and short RST to GND: fit the
switch by two diagonal legs only).

| jumper | bridge to | left half | right half |
|---|---|---|---|
| `JP1` RAW | centre -> L or R | pad 1 = `RAW` | pad 24 = `RAW` |
| `JP2` GND | centre -> L or R | pad 21 = `GND` | pad 4 = `GND` |

## Assembly

1. Pick your half and work on **that face only** -- the one whose silkscreen names your half.
2. Diodes: cathode (the bar) towards the marked end. The land takes a SOD-123 on either face, or a
   through-hole 1N4148 bent to 3.3 mm.
3. Hot-swap sockets, one per key, on the same face -- the silkscreen outlines each one, so the
   socket goes where its outline is. **Right half: rotated 180 degrees**; the outlines on that face
   are drawn that way round, so follow them rather than the other side's.
4. Reset and slide switch: through-hole, bodies on the *other* face -- they poke up through their
   windows in the plate.
5. Sockets for the controller on the **other** face -- the plate side, with the reset and slide
   switch bodies. The nano sits on top of the board, **component side down** (towards the board:
   its USB shell lives in the 3.5 mm socket gap), USB towards the notch in the wall, and finishes
   flush in the plate's window. The nano's own B+ / B- pads stay empty; the battery reaches it
   through RAW / GND -- *after* the slide switch, so **charge with the switch on**: switched off, the
   charger sees no cell and its blue LED blinks instead of charging.
6. Bridge `JP1` and `JP2` to the pad marked for your half.
7. Battery leads to `BAT +` / `-`; they drop through the plate's controller window from the pod above.

## Bill of materials (per half)

| qty | part | notes |
|---|---|---|
| 20 | Kailh MX hot-swap socket | CPG151101S11, one per key, on the face you assemble |
| 20 | 1N4148W diode | SOD-123; a through-hole 1N4148 on 3.3 mm pitch fits the same land |
| 20 | MX switch | plate-mount 3-pin or PCB-mount 5-pin, 3x 1.25u for the thumbs |
| 1 | nice!nano v2 / nRF52840 SuperMini | component side DOWN on 3.5 mm low-profile sockets |
| 2 | 1x12 machined low-profile socket | Mill-Max and similar; a normal stamped 2.54 header stands ~8.5 mm and will not fit under the plate |
| 2 | 1x12 machined pin strip | into the controller's castellations, pins out of its COMPONENT side. Measure board surface to controller underside with a pin seated: that is mcu_socket_h (3.5 mm by default, and it cannot go below 3.5 -- the USB shell hangs 3.2 mm under the board) |
| 1 | 12x12 mm THT tactile switch | reset, tall plunger, through the plate window |
| 1 | SS12D00 slide switch | power, through the plate window |
| 1 | LiPo cell 902030 (9.5 x 20 x 30, 500 mAh) | in a pod moulded into the plate, directly over the controller |

Plus, from the case: 8 x M2x3x3.5 heat-set inserts, 8 x M2x10 screws, 8 x 10 mm bumpons.

## Why the mounting holes are notches

Five of the eight are half-circles in the edge rather than holes through the board; the other three
(the thumb end, the bay's bottom corner and the one between the columns) are real holes. That follows
from the case: five of its screw bosses sit 0.5 mm inside the inner wall line so they merge into the
wall, and the board is the cavity less 0.5 mm -- so those screws' centres land exactly on the board's
edge. The other three bosses stand 2.5-3 mm clear of the wall, because the wall keeps rising past the
bosses in this build and an insert hole at the wall line would be tucked under it; the five that stay
on the line get a 4 mm channel up the inside of the wall instead, so their inserts and screws drop in.

Nothing is bolted through the board. It is **clamped**: the case's 6 mm bosses come up to its
underside and the plate's 5 mm spacer bosses come down onto its top, about 8 mm2 of board between
them at each point, and the M2 screw passes through the notch on its way from the plate into the
boss. The notches also locate the board -- each one hugs a screw shank, so the board cannot shift in
the 0.5 mm of slack around it. Fit the board with the screws out, then drop them through.

## Ordering

Two-layer, 1.6 mm, any finish, no controlled impedance. `pacino_pod_gerbers.zip` is ready to upload.
Order it twice over (or ten boards, which is the usual minimum) -- the same board is both halves.

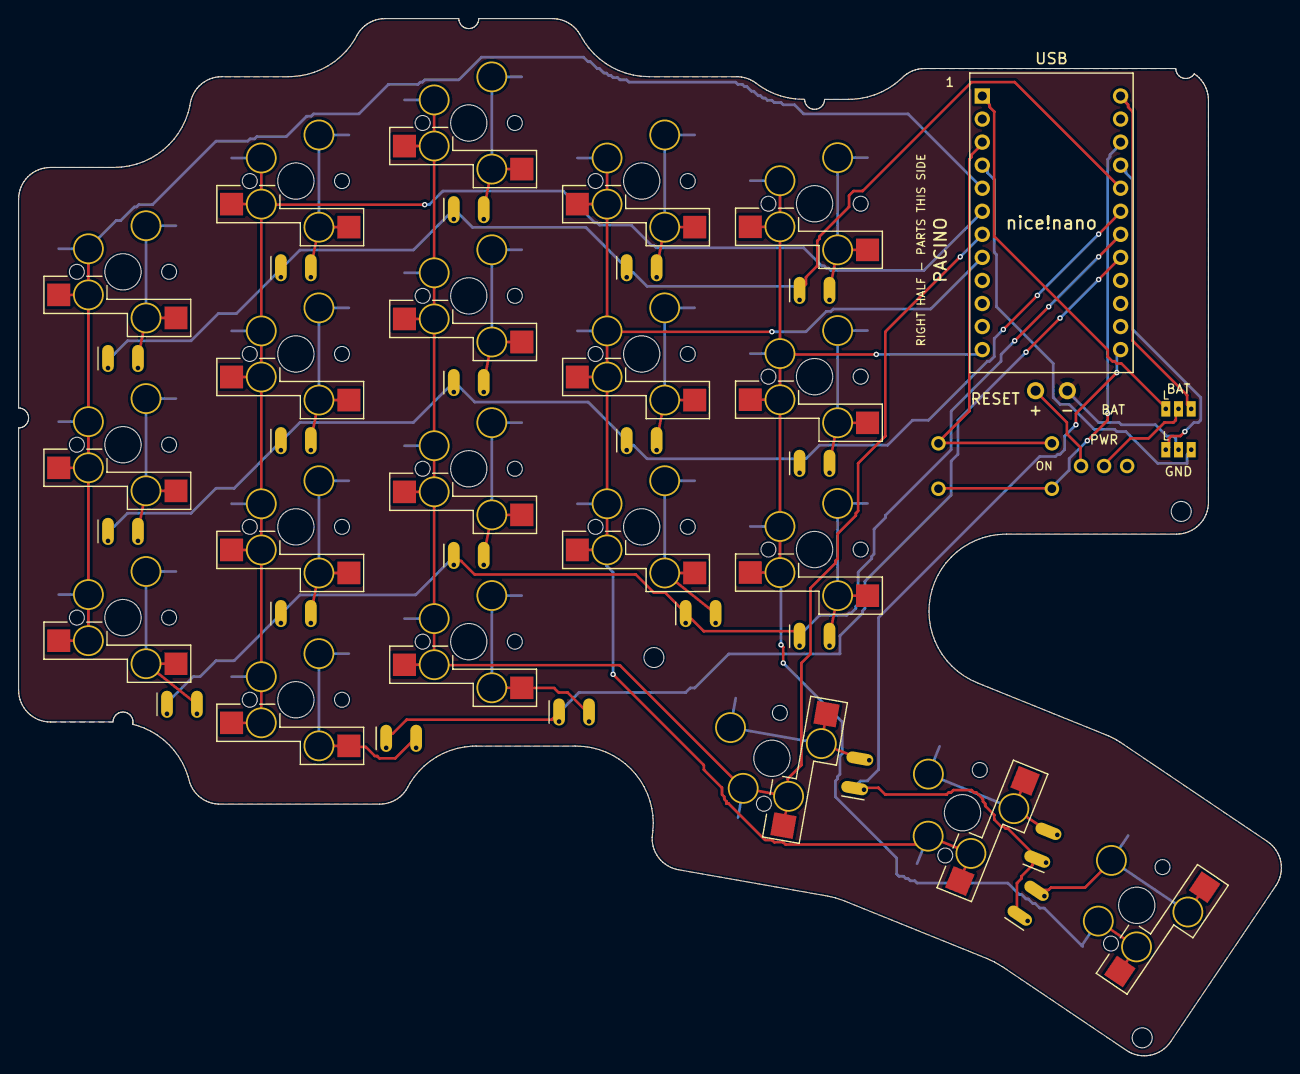
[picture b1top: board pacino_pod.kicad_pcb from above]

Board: 2 copper layers, 139.1 x 114.3 mm, 49 parts (0 on the bottom side), 39 nets.

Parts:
BT1: LiPo
D1, D2, D3, D4, D5, D6, D7, D8, D9, D10, D11, D12, D13, D14, D15, D16, D17, D18, D19, D20: 1N4148W
H1, H2, H3: MountingHole
JP1: BAT_SELECT
JP2: GND_SELECT
PWR1: SS12D00
RSW1: SW_Tactile_12mm
SW1, SW2, SW3, SW4, SW5, SW6, SW7, SW8, SW9, SW10, SW11, SW12, SW13, SW14, SW15, SW16, SW17, SW18, SW19, SW20: MX_Hotswap_Rev
U1: nice!nano

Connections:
BAT_L: JP1.1, U1.1
BAT_P: BT1.1, PWR1.1
BAT_R: JP1.3, U1.24
BAT_SW: JP1.2, PWR1.2
COL0: SW1.1, SW2.1, SW3.1, U1.5
COL1: SW4.1, SW5.1, SW6.1, SW16.1, U1.6
COL2: SW7.1, SW8.1, SW9.1, SW17.1, SW18.1, U1.7
COL3: SW10.1, SW11.1, SW12.1, SW19.1, U1.8
COL4: SW13.1, SW14.1, SW15.1, SW20.1, U1.12
GND: BT1.2, JP2.2
GND_L: JP2.1, U1.21
GND_R: JP2.3, U1.4
ROW0: D3.1, D6.1, D9.1, D12.1, D15.1, U1.20
ROW1: D2.1, D5.1, D8.1, D11.1, D14.1, U1.19
ROW2: D1.1, D4.1, D7.1, D10.1, D13.1, U1.18
ROW3: D16.1, D17.1, U1.17
ROW4: D18.1, D19.1, D20.1, U1.13
RST_A: RSW1.1, U1.3
RST_B: RSW1.2, U1.22
SW1: D1.2, SW1.2
SW2: D2.2, SW2.2
SW3: D3.2, SW3.2
SW4: D4.2, SW4.2
SW5: D5.2, SW5.2
SW6: D6.2, SW6.2
SW7: D7.2, SW7.2
SW8: D8.2, SW8.2
SW9: D9.2, SW9.2
SW10: D10.2, SW10.2
SW11: D11.2, SW11.2
SW12: D12.2, SW12.2
SW13: D13.2, SW13.2
SW14: D14.2, SW14.2
SW15: D15.2, SW15.2
SW16: D16.2, SW16.2
SW17: D17.2, SW17.2
SW18: D18.2, SW18.2
SW19: D19.2, SW19.2
SW20: D20.2, SW20.2

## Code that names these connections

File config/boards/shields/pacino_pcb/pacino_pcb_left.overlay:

#include "pacino_pcb.dtsi"

/*
 * Left half: sockets and diodes on the board's BACK face, controller on the FRONT (on top of the
 * board, component side down).  Seen from the front that puts the nano's RAW row on pads 13-24 and
 * its TX row on pads 1-12.  Bridge JP1 / JP2 to the pad marked L, on the face the nano sits on.
 */

&kscan0 {
    row-gpios
        = <&pro_micro 2 (GPIO_ACTIVE_HIGH | GPIO_PULL_DOWN)>    /* row 0: top    */
        , <&pro_micro 3 (GPIO_ACTIVE_HIGH | GPIO_PULL_DOWN)>    /* row 1: home   */
        , <&pro_micro 4 (GPIO_ACTIVE_HIGH | GPIO_PULL_DOWN)>    /* row 2: bottom */
        , <&pro_micro 5 (GPIO_ACTIVE_HIGH | GPIO_PULL_DOWN)>    /* row 3: extras */
        , <&pro_micro 9 (GPIO_ACTIVE_HIGH | GPIO_PULL_DOWN)>    /* row 4: thumbs */
        ;
    /* COL0 .. COL4 = pinky .. inner, the order the transform wants for the left half */
    col-gpios
        = <&pro_micro 21 GPIO_ACTIVE_HIGH>   /* col 0: pinky  (COL0) */
        , <&pro_micro 20 GPIO_ACTIVE_HIGH>   /* col 1: ring   (COL1) */
        , <&pro_micro 19 GPIO_ACTIVE_HIGH>   /* col 2: middle (COL2) */
        , <&pro_micro 18 GPIO_ACTIVE_HIGH>   /* col 3: index  (COL3) */
        , <&pro_micro 10 GPIO_ACTIVE_HIGH>   /* col 4: inner  (COL4) */
        ;
};
